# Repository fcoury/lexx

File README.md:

# KobitoKey-inspired folding keyboard

## Expanded hot-swap keyboards

Both editions have **58 south-facing switches**, a 19.05 mm finger pitch, and three folding thumb keys per hand. Choose the PCBs, plates and sockets for your switches.

| Switch edition | Complete package | Build guide |
| --- | --- | --- |
| Full-height MX · revision B | [Download MX](Expanded-MX-PCB.zip) | [MX parts and assembly](pcb/README.md) |
| Low-profile Kailh Choc V2 | [Download Choc V2](Expanded-Choc-V2-PCB.zip) | [Choc V2 parts and assembly](choc-v2/README.md) |

## Hand-wired MX case

The standard model preserves the 17 finger positions and three-key thumb fan on each hand. The expanded model adds a far row and an outer column to the main grid, bringing each hand to 29 switches. Both use the same thumb shell, hinge and thumb plate. The instructions below cover the hand-wired mechanical prototype. The [hinge sourcing notes](hinge-sourcing.md) cover two commercial torque-hinge candidates.

## Layout and source

The standard finger matrix uses 19.05 mm pitch. The three thumb switches follow the original fan in front of the inner finger columns. Their center spacing scales with the original layout, so it is wider than one finger-key pitch. The return beside the finger deck is closed for this trackball-free build. A future sensor, ball retainer and controller mount would require their own mechanical design.

The switch positions came from measurements of the maker’s v1.0.1 plate openings. Coordinates below are for the left hand, relative to the innermost front finger switch. Positive X points inward and positive Y points toward the far row. The right hand mirrors X and yaw.

| Thumb key | X at MX scale | Y at MX scale | Yaw |
|---|---:|---:|---:|
| Under finger bank | −12.70 mm | −38.83 mm | 0° |
| Middle | +10.33 mm | −41.64 mm | −14° |
| Inner tip | +32.02 mm | −49.96 mm | −28° |

The extra row sits beyond the existing back row. The new outer column follows the pinky stagger. All 20 original positions stay fixed relative to the index key. In the saved files, the added nine cap proxies per hand form a separate object named `fixed_caps_added`.

[Measured layout overlay](layout-fit.png) · [Maker’s CAD release](https://github.com/juichi50iii/KobitoKey_QWERTY/releases/tag/v1.0.1) · [Product site](https://juichi50iii.github.io/kobitokey-site/) · [Kit listing](https://iikagen-11.booth.pm/items/7511680)

## Open and pose

1. Open `models/Standard.blend` or `models/Expanded.blend`. The **Controls** object is selected.
2. In **Object Properties → Custom Properties**, drag **thumb_fold_deg** or enter a number from 0 to 60. The finger deck stays fixed in this editing scene.
3. To inspect both hands, use Blender’s scene selector to switch to **Split keyboard** and press **Home** over the viewport to frame the pair. The right half mirrors edits and fold adjustments to the left.
4. Hide the purchased-parts collection to inspect the bare case. The shaded switches and dished caps are fit and visualization proxies. Every printable part is a separate mesh. The source scripts are included alongside the models and in Blender’s Text Editor.

The angle is between decks. For use at 60°, tip the entire half onto the outer edges of both shells to form a tent. The main deck then sits roughly 12° above the desk on the standard half and 11° on the expanded half. The indexed lock holds **flat or folded**. Remove the locking screw to move between those positions.

## Print and assemble

Print one each of the four STLs in each hand folder for the chosen variant, eight parts per keyboard. The hand-specific files are already mirrored. Import in millimeters at 100%. The shells are floor-down and the removable plates are top-face-down with their posts pointing up. The nominal switch openings are 14.00 mm square through a 1.50 mm plate.

| Per half | Quantity | Fit |
|---|---:|---|
| MX-compatible 1u switches and caps | 20 standard or 29 expanded | 18.2 mm square keycap envelope used for fold testing |
| M3 × 50 socket-head screw and M3 nyloc nut | 1 each | Axle, 3.5 mm printed bores, head up to Ø5.5 × 3 mm, nut up to Ø6.4 × 4 mm; no washers |
| M3 × 10 socket-head screw | 1 | Removable angle lock, same head envelope |
| M3 brass heat-set insert | 1 | Ø4.0 × 4.0 mm body, Ø3.65 mm modeled pilot. Match the insert supplier’s pilot recommendation to your material |
| M2.5 × 8 countersunk plastic thread-forming screws | 9 | Five finger plate posts and four thumb plate posts, 2.1 mm blind pilot, 90° countersink, head diameter up to 5.1 mm |

1. Print one thumb plate to check switch retention and one shell pair to check the hinge before committing to the full keyboard. PETG with a 0.4 mm nozzle, 0.2 mm layers and four walls is a starting point for shells. Use a layer height that reproduces the 1.5 mm plate thickness, such as 0.15 mm. Support the horizontal knuckles locally and clear their bores before assembly.
2. With the thumb shell detached, press the heated insert flush into its **single offset bore**, from the rear (+Y) face of the moving ear. The main shell’s matching ear has two offset holes. The central holes take the axle.
3. Interleave the knuckles with the shells flat. Lift the case and hold the axle nut against the forward fixed ear from below. Feed the M3 × 50 axle from the rear. Leave it free enough to pivot without pulling the knuckles together.
4. Snap switches into the plates and hand-wire them. Use the paired rear ports for a flexible external service loop behind the hinge. Route the host/controller lead through the separate rear opening on the finger shell. Size and secure the loop on the actual assembly across the full fold. Electronics, strain relief and a controller-specific cradle are left to the builder.
5. Lower each plate onto its shell and fit the M2.5 screws from underneath. At 0° or 60°, pass the M3 × 10 locking screw through the aligned fixed-ear hole and into the insert. Remove it fully before changing angle.

[Exploded view](case-parts.png)

## Verification and limits

Both editable models were generated and reopened with Blender 5.2.4 LTS. The fold validator evaluates both ends and 119 intermediate poses. It checks every fixed mesh against every moving mesh, including hidden 18.2 mm full-stroke switch/keycap envelopes and the axle. The continuous lower bound subtracts the maximum possible motion between samples. The second hand is an exact reflection.

The smallest sampled gap was 0.248 mm at the axle. The conservative lower bound over the whole fold was 0.205 mm there and 0.4995 mm between printed parts.

The STL checker reads each exported file independently, tests topology and self-intersections, and probes switch apertures, mounting holes, switch-body clearance and cable passages. A separate hardware check examines screw, nut and insert fit and access. The reports record file hashes and the assumptions used.

No physical print, typing-load test, wire-flex life test or printer-tolerance study has been performed. Printer shrinkage, cap profile, switch clips and insert dimensions can change the fit.

[Standard fold report](validation/Standard.json) · [Expanded fold report](validation/Expanded.json) · [Hardware report](validation/hardware.json) · [STL report](validation/parts.json)

## Rebuild

From this folder, using fish on macOS, run the following commands. In Codex on this Mac, run all Blender commands outside the sandbox per AGENTS.md.

```fish
set blender_bin /Applications/Blender.app/Contents/MacOS/Blender
$blender_bin -b --factory-startup --python-exit-code 1 --python build.py
for variant in Standard Expanded
    $blender_bin -b models/$variant.blend --python-exit-code 1 --python validate_fold.py -- --max-step 0.5 --output validation/$variant.json
end
$blender_bin -b --factory-startup --python-exit-code 1 --python validate_hardware.py
python3 validation/check_parts.py
python3 preview.py
```

The STL checker uses NumPy. The preview script uses Pillow and invokes Blender to render the saved models.

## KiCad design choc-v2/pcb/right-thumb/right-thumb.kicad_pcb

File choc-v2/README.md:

# Expanded Choc V2 keyboard

This low-profile split uses **58 south-facing Kailh Choc V2 switches**. Each hand has 26 finger keys and a folding three-key thumb fan. It keeps the 19.05 mm finger pitch, key centers and thumb angles of the expanded MX keyboard. The Choc plate sits 2.20 mm above the top of the PCB, 2.80 mm closer than the MX plate. Both editions use the indexed M3 hinge and a separate wireless controller per hand.

## Parts for one keyboard

Use 58 **Kailh PG1353** switches, 58 **Kailh CPG135001S30** hot-swap sockets and 58 low-profile 1u keycaps specified for the Choc V2 cross stem. Red linear **CPG135301D01** is the dimensional reference for this version. The asymmetric retention slot is on the LED side. The switch windows face the typist from the keycap side and follow each thumb key’s angle. This version has no per-key LED circuit. [Switch drawings](https://www.kailh.net/pages/product-datasheet) · [Socket drawing](https://cdn-shop.adafruit.com/product-files/5118/5118-Choc-Socket.pdf) · [Purchasing BOM](BOM.csv)

| Board (one each) | Editable KiCad project | Gerbers and drills |
| --- | --- | --- |
| Left finger | [Project](pcb/left-finger/left-finger.kicad_pro) | [Fabrication ZIP](pcb/fabrication/left-finger-fabrication.zip) |
| Left thumb/controller | [Project](pcb/left-thumb/left-thumb.kicad_pro) | [Fabrication ZIP](pcb/fabrication/left-thumb-fabrication.zip) |
| Right finger | [Project](pcb/right-finger/right-finger.kicad_pro) | [Fabrication ZIP](pcb/fabrication/right-finger-fabrication.zip) |
| Right thumb/controller | [Project](pcb/right-thumb/right-thumb.kicad_pro) | [Fabrication ZIP](pcb/fabrication/right-thumb-fabrication.zip) |

[View the routed boards](pcb/preview.png) · [Switch, fabrication and firmware checks](validation/README.md)

## Build a first pair

1. **Test one switch.** Print the [one-switch fit coupon](case/choc-fit-coupon.stl) using the same filament, layer height and slicer compensation you intend to use for the plates. Check that the rim rests flat, the clips engage, and your keycap reaches full travel without rubbing. Print the [two A4 fit sheets](fit-sheets.pdf) at Actual Size and check the 50 mm bar with a ruler.
2. **Print one hand.** Select its fixed shell, fixed plate, thumb shell and thumb plate from the [case files](case/print/). Dry-fit the hardware and boards, starting with the moving thumb deck. To inspect the assembly digitally, select Controls in the [Blender model](case/Expanded-Choc-V2.blend) and adjust the thumb fold angle from 0° to 60°. Install the angle-lock screw for use at 0° or 60°.
3. **Order four different boards.** Upload each fabrication ZIP separately. Specify two-layer 1.6 mm FR-4, 1 oz copper and unplated routed slots. Check each handed outline and verify the offset retention slots in the fabricator’s drill preview. The placement CSVs and inspection reports accompany the [fabrication archives](pcb/fabrication/).
4. **Assemble the backs.** Fit a Choc socket and SOD-123 diode at each switch position. The diode band goes to pad 1. Fit the Hirose J1 flex connector on each board. Fit the XIAO nRF52840 directly to its lands (including underside battery and ground lands), S1, and the J2 battery jack on each thumb board. Assemble the matrix first on USB. The XIAO modules provide USB-C, battery charging and Bluetooth. [Controller documentation](https://wiki.seeedstudio.com/XIAO_BLE/)
5. **Connect and test.** Fit a 12-position 0.50 mm-pitch ribbon with opposite-side contacts and 0.30 mm mating tips. With power off, check J1 pin 1 to pin 1 through 12 to 12. Check for shorts between the battery supply and ground. Check J2 lead polarity before fitting an optional protected cell. Flash the [left and right firmware](firmware/README.md), test all 29 positions per hand and support each socket while inserting its switch.
6. **Exercise the fold.** Route a slack loop behind the hinge and protect it at the shell openings. With the angle-lock screw removed, move slowly through the range and check for cable tension, creasing, rubbing, desk contact and dropped keys. The rigid-part simulation leaves cable flex life, print tolerances, radio range and assembled operation for a physical prototype. [Case and fold checks](case/README.md)

## Editing

Keep each KiCad project beside the supplied symbol, footprint and model libraries. The four native boards are the manufacturing masters. The [firmware configuration](firmware/config/) contains the matrix and three keymap layers. The build uses the name **Lexx Choc V2** over Bluetooth so you can distinguish it from **Lexx MX**.

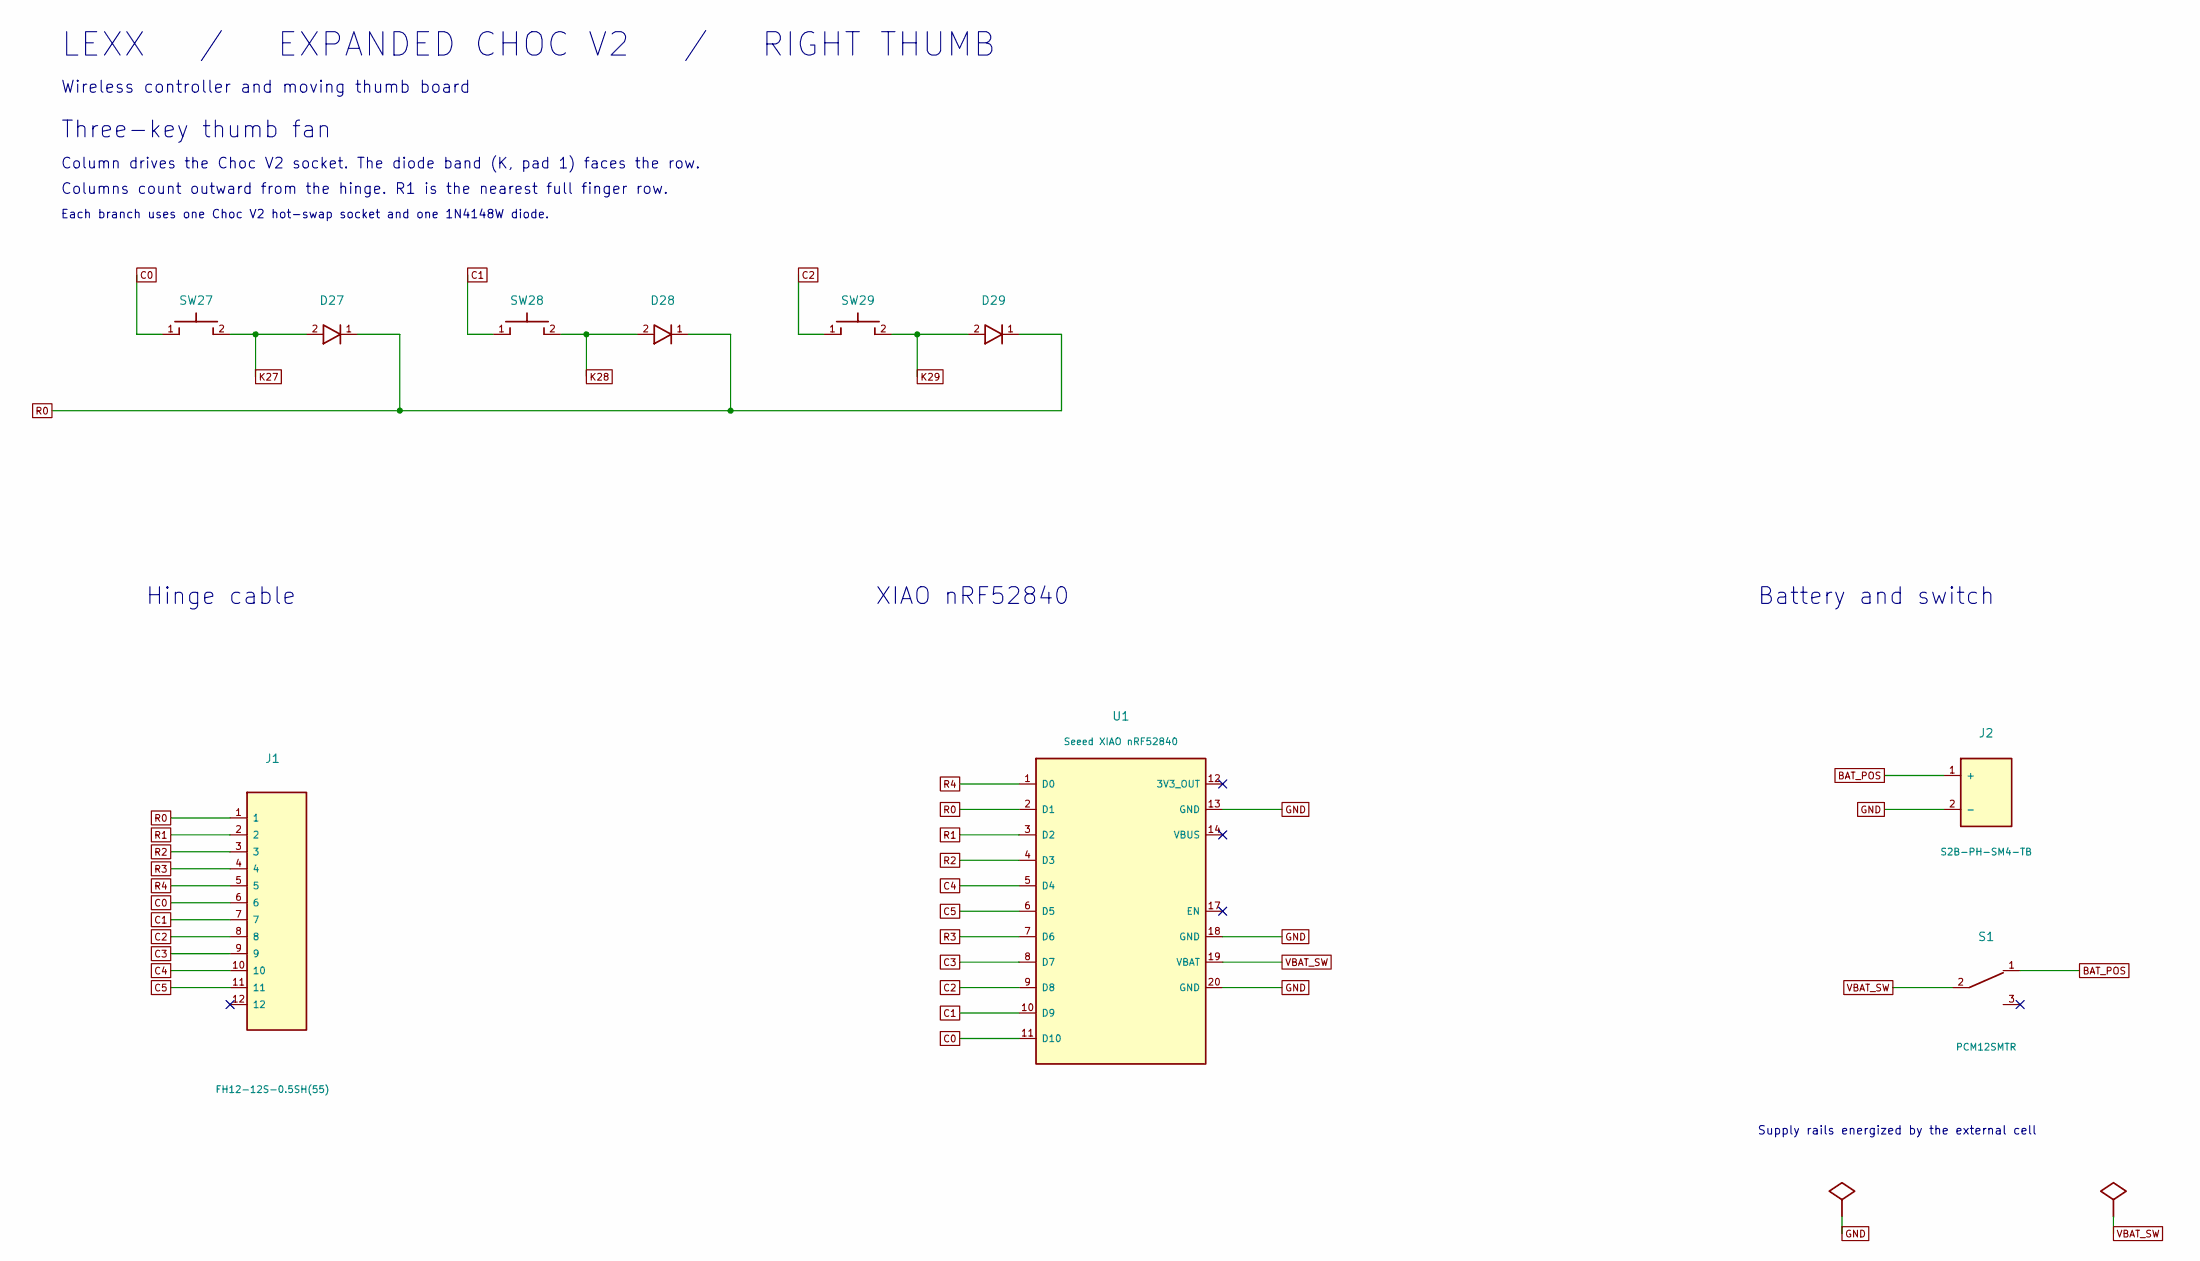
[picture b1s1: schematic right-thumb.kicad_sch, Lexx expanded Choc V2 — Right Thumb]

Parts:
D27, D28, D29: 1N4148W; SOD123
J1: FH12-12S-0.5SH(55); FFC12
J2: S2B-PH-SM4-TB; Battery
S1: PCM12SMTR; PowerSwitch
SW27, SW28, SW29: PG1353 / CPG135001S30; ChocV2
U1: Seeed XIAO nRF52840; XIAO

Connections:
BAT_POS: J2.1 (+), S1.1
C0: J1.6, SW27.1, U1.11 (D10)
C1: J1.7, SW28.1, U1.10 (D9)
C2: J1.8, SW29.1, U1.9 (D8)
C3: J1.9, U1.8 (D7)
C4: J1.10, U1.5 (D4)
C5: J1.11, U1.6 (D5)
GND: J2.2 (−), U1.13 (GND), U1.18 (GND), U1.20 (GND)
K27: D27.2 (A), SW27.2
K28: D28.2 (A), SW28.2
K29: D29.2 (A), SW29.2
R0: D27.1 (K), D28.1 (K), D29.1 (K), J1.1, U1.2 (D1)
R1: J1.2, U1.3 (D2)
R2: J1.3, U1.4 (D3)
R3: J1.4, U1.7 (D6)
R4: J1.5, U1.1 (D0)
VBAT_SW: S1.2 (COM), U1.19 (VBAT)

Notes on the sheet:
Three-key thumb fan
Column drives the Choc V2 socket. The diode band (K, pad 1) faces the row.
Columns count outward from the hinge. R1 is the nearest full finger row.
Each branch uses one Choc V2 hot-swap socket and one 1N4148W diode.
LEXX / EXPANDED CHOC V2 / RIGHT THUMB
Wireless controller and moving thumb board
Hinge cable
XIAO nRF52840
Battery and switch
Supply rails energized by the external cell

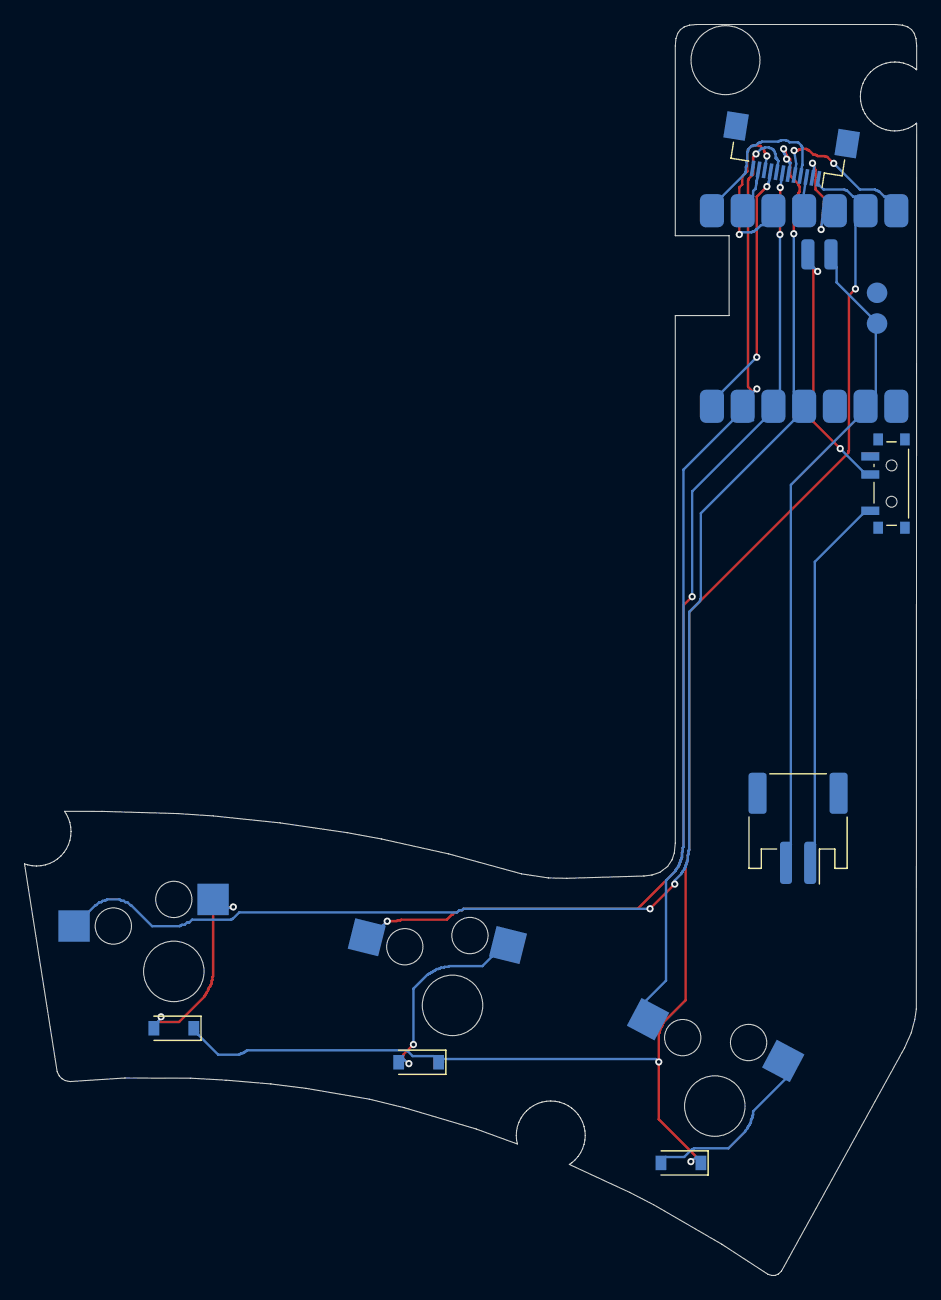
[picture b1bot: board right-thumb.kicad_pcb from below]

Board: 2 copper layers, 73.8 x 103.4 mm, 10 parts (10 on the bottom side), 17 nets.

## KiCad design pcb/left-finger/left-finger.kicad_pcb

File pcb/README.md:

# Expanded MX hot-swap PCB · Revision B

All **58 MX switches face south**. Looking down at the keys, the LED window sits on the edge nearest the typist. Each thumb switch follows its angled keycap. This revision uses Kailh hot-swap sockets and has no per-key lighting circuit.

Each hand has a passive 26-key finger PCB and a three-key moving thumb PCB. The thumb board carries a Seeed XIAO nRF52840, USB-C, the battery connector and the power switch. One 12-conductor flex cable connects the two boards within a hand. The left and right controllers communicate over Bluetooth. Revision B retains the original 19.05 mm finger pitch and three thumb centers, and uses the indexed 0–60° hinge.

[View the copper layers on all four boards](preview.png).

The [populated left-hand underside](left-assembly.png) shows the Kailh sockets and the thumb controller at their flat-case positions. The controller and battery connector use simplified package models.

## Files for one keyboard

| Board | Editable KiCad 10 project | Fabrication archive | Quantity |
| --- | --- | --- | --- |
| Left finger | [Project](left-finger/left-finger.kicad_pro) | [Gerbers and drills](fabrication/left-finger-fabrication.zip) | 1 |
| Left thumb/controller | [Project](left-thumb/left-thumb.kicad_pro) | [Gerbers and drills](fabrication/left-thumb-fabrication.zip) | 1 |
| Right finger | [Project](right-finger/right-finger.kicad_pro) | [Gerbers and drills](fabrication/right-finger-fabrication.zip) | 1 |
| Right thumb/controller | [Project](right-thumb/right-thumb.kicad_pro) | [Gerbers and drills](fabrication/right-thumb-fabrication.zip) | 1 |

Keep the project folders together with the shared symbol and footprint libraries. Each project contains its own editable schematic and routed board. Each archive describes a separate **two-layer, 1.6 mm FR-4 bare PCB**. Specify 1 oz copper. Import all layers and both drill types in millimeters and preserve handedness.

Use the [purchasing BOM](BOM.csv), [PCB case and printable shells](case/README.md), [production files and placement CSVs](fabrication/) and [firmware and flashing instructions](firmware/README.md). Use the revision B finger shells and finger plates together. The central screw moves 3.77 mm toward the rear, and the rear edge extends around the relocated flex connector. The [case print guide](case/README.md) identifies the matching parts for both hands.

## What follows the original

The original kit and build guide establish the two-board layout, flexible link, controller location and diode matrix. The published firmware gives the XIAO GPIO assignments. The maker's public release provided case models and firmware. The schematics, routing, hot-swap placements and expanded matrix here were designed for the new MX case. The nine added switches per hand need six columns and five rows. The original 10-position flex is too small for that passive matrix. All 11 header GPIOs now serve the keyboard, so a later trackball requires a new interface. [Design sources and footprint credits](ATTRIBUTION.md)

| J1 pin | 1 | 2 | 3 | 4 | 5 | 6 | 7 | 8 | 9 | 10 | 11 | 12 |
| --- | --- | --- | --- | --- | --- | --- | --- | --- | --- | --- | --- | --- |
| Signal | R0 | R1 | R2 | R3 | R4 | C0 | C1 | C2 | C3 | C4 | C5 | unused |
| XIAO pin | D1 | D2 | D3 | D6 | D0 | D10 | D9 | D8 | D7 | D4 | D5 | — |

Each switch connects a column to the anode of its diode. The cathode connects to the row. R0/C0 through R0/C2 are the original thumb fan. The two lower pinky-side finger positions occupy R0/C3 and R0/C4. R0/C5 is open. SW1–SW26 live on the finger PCB. SW27–SW29 live on the thumb PCB. Reference numbers repeat on the opposite hand.

## Assemble and bring up the first pair

1. **Check fit on paper.** Print the [two A4 fit sheets](expanded-mx-fit-sheets.pdf) at actual size. Measure the 50 mm scale bar and align the switch centers and post holes against the matching revision B plate. The marks beside the centers identify the LED-window side. Use the revised shells for access to USB, the battery switch and the flex.
2. **Populate the backs.** Fit the bottom-side Kailh sockets and SOD-123 diodes. The cathode band goes to pad 1. Both J1s use the same Hirose bottom-contact socket. The XIAO's own USB-C jack points toward the outer side of the thumb return. Fit the module directly to its lands without pin headers. Paste/reflow the required underside battery and ground lands with the castellations. The USB data lines and charge controller are on the module. [Kailh MX socket](https://www.kailhswitch.com/info/kailh-pcb-socket-for-switch-37972215.html) · [Hirose connector drawing](https://www.hirose.com/product/p/CL0586-0704-0-55) · [Seeed controller documentation](https://wiki.seeedstudio.com/XIAO_BLE/)
3. **Fit the flex.** Use 12 ways, 0.50 mm pitch, opposite-side exposed contacts and 0.30 mm mating tips. A 102 mm jumper is the starting length. Insert both ends fully and close both latches. With power disconnected, check J1 pad 1 to pad 1, then 2 to 2 through 12 to 12. Route a slack loop through the two rear openings and behind the axle. The flex should stay clear of the screws and desk throughout the fold. Check the cable supplier's dynamic bend limits. [Molex candidate](https://www.molex.com/en-us/products/part-detail/150782412)
4. **Check power without a battery.** On the unpowered board, check for shorts between BAT_POS, VBAT_SW, ground and the module's 3V3 pad. S1 should connect J2 pin 1 to U1 pad 19 in only one position. J2 pin 2 should connect to ground in either position. Power each XIAO by USB and flash the matching [left](firmware/bin/lexx_left.uf2) or [right](firmware/bin/lexx_right.uf2) image. Pair the halves. Momentarily bridge the two switch contacts at each position to test the matrix before installing the switches.
5. **Install the switches.** Looking down at a flat hand with the thumb keys nearest you, point each LED window toward you. On an angled thumb key, the LED window follows the near edge of that keycap. Align the two metal pins with the socket openings before pressing. Support the socket from behind during installation. Check the chosen keycap profile through a full stroke on the narrow pinky column and the three thumb keys.
6. **Fit the optional batteries.** Use one protected 1S LiPo per side, within the case's 18 × 24 × 4 mm body envelope, with a charge-current rating suitable for the XIAO. Verify the actual lead polarity with a meter before mating the plug. Pin 1 is positive. Pin 2 is ground. The battery charges through the XIAO when S1 connects it. S1 disconnects the battery in the other position. USB can still power the module. Secure the pack and leave the plug, flex and antenna clear.
7. **Exercise the hinge.** Test several chords across both halves at 0° and 60°. Move slowly through intermediate positions with the index screw removed. Check for key dropouts, cable tension, creasing or rubbing. Verify wireless range and check USB plug access with the cable and shell you plan to use.

## Verification and scope

KiCad's ERC checks the schematic. DRC checks the board geometry and copper connections, including schematic parity. All four boards passed ERC and DRC with zero warnings, errors, open connections or schematic mismatches. The per-board reports live beside the Gerbers. The case checks compare the actual board outlines with the printed shells and plate posts. Each board sits with its top 5 mm beneath the plate top. The smallest PCB-to-shell gap is 0.38 mm. The socket bodies clear the shell by at least 0.99 mm. Both hands retain at least 1.0 mm of clearance between the rigid electronics and the opposing deck or hinge hardware through 0–60°. [Measured case fit](case/board-fit.json) · [Rigid fold sweep](case/fold.json) · [Electronics fold sweep](case/electronics-fold.json)

The fold sweep covers the rigid parts and switch/keycap envelopes. Cable fatigue, battery-lead routing, RF range, USB plug overmold clearance, typing load, solder assembly and printer tolerance need physical testing. The printable shells use the indexed M3 hinge. The optional Ø4 × 11 mm commercial hinge takes a separate keyed mount.

## Recheck a design

Open a project in KiCad to edit the schematic or copper. To check all four projects from a terminal, put KiCad 10's CLI on PATH and run these commands from this directory.

```fish
python3 tools/verify_matrix.py
for board in left-finger left-thumb right-finger right-thumb
    kicad-cli sch erc --exit-code-violations -o /tmp/$board-erc.rpt $board/$board.kicad_sch
    kicad-cli pcb drc --schematic-parity --exit-code-violations -o /tmp/$board-drc.rpt $board/$board.kicad_pcb
end
```

Run `tools/verify_switches.py` with KiCad’s Python interpreter (`pcbnew`) to check the physical contact and locating holes against the intended LED-window direction, key centers, and matrix. To regenerate the A4 fit sheets, run `python3 tools/fit_sheet.py --kicad-python /path/to/kicad/python3` with ReportLab available to the outer interpreter.

The routed KiCad boards are the manufacturing masters. To replot one, use KiCad's Python interpreter with the `pcbnew` module and run `tools/route_and_plot.py left-finger/left-finger.kicad_pcb --output fabrication`. For a new layout, use a separate checkout. `tools/plan.py` (Python with Shapely) derives the outlines from the case. `tools/schematics.py` builds the diagrams from the pin manifests and `tools/place.py` builds fresh, unrouted boards with KiCad's Python. Routing includes hand finishing. Recheck schematic parity, copper, physical fit and the firmware matrix after changing geometry.

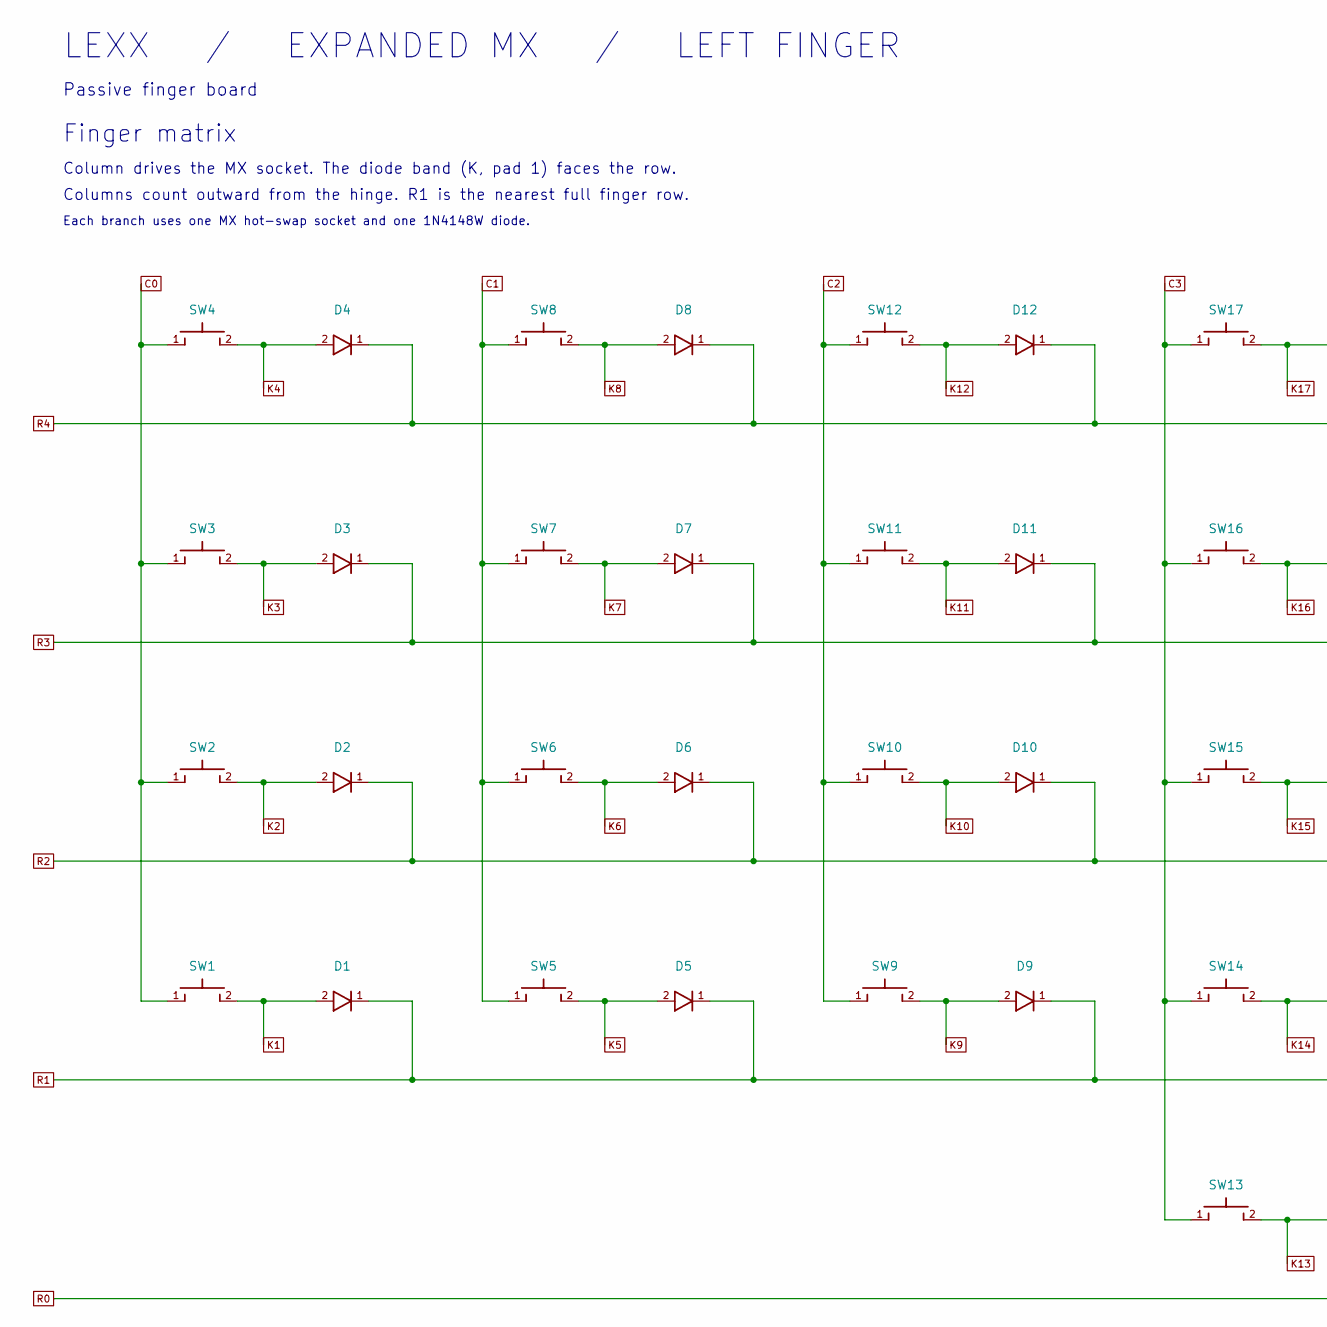
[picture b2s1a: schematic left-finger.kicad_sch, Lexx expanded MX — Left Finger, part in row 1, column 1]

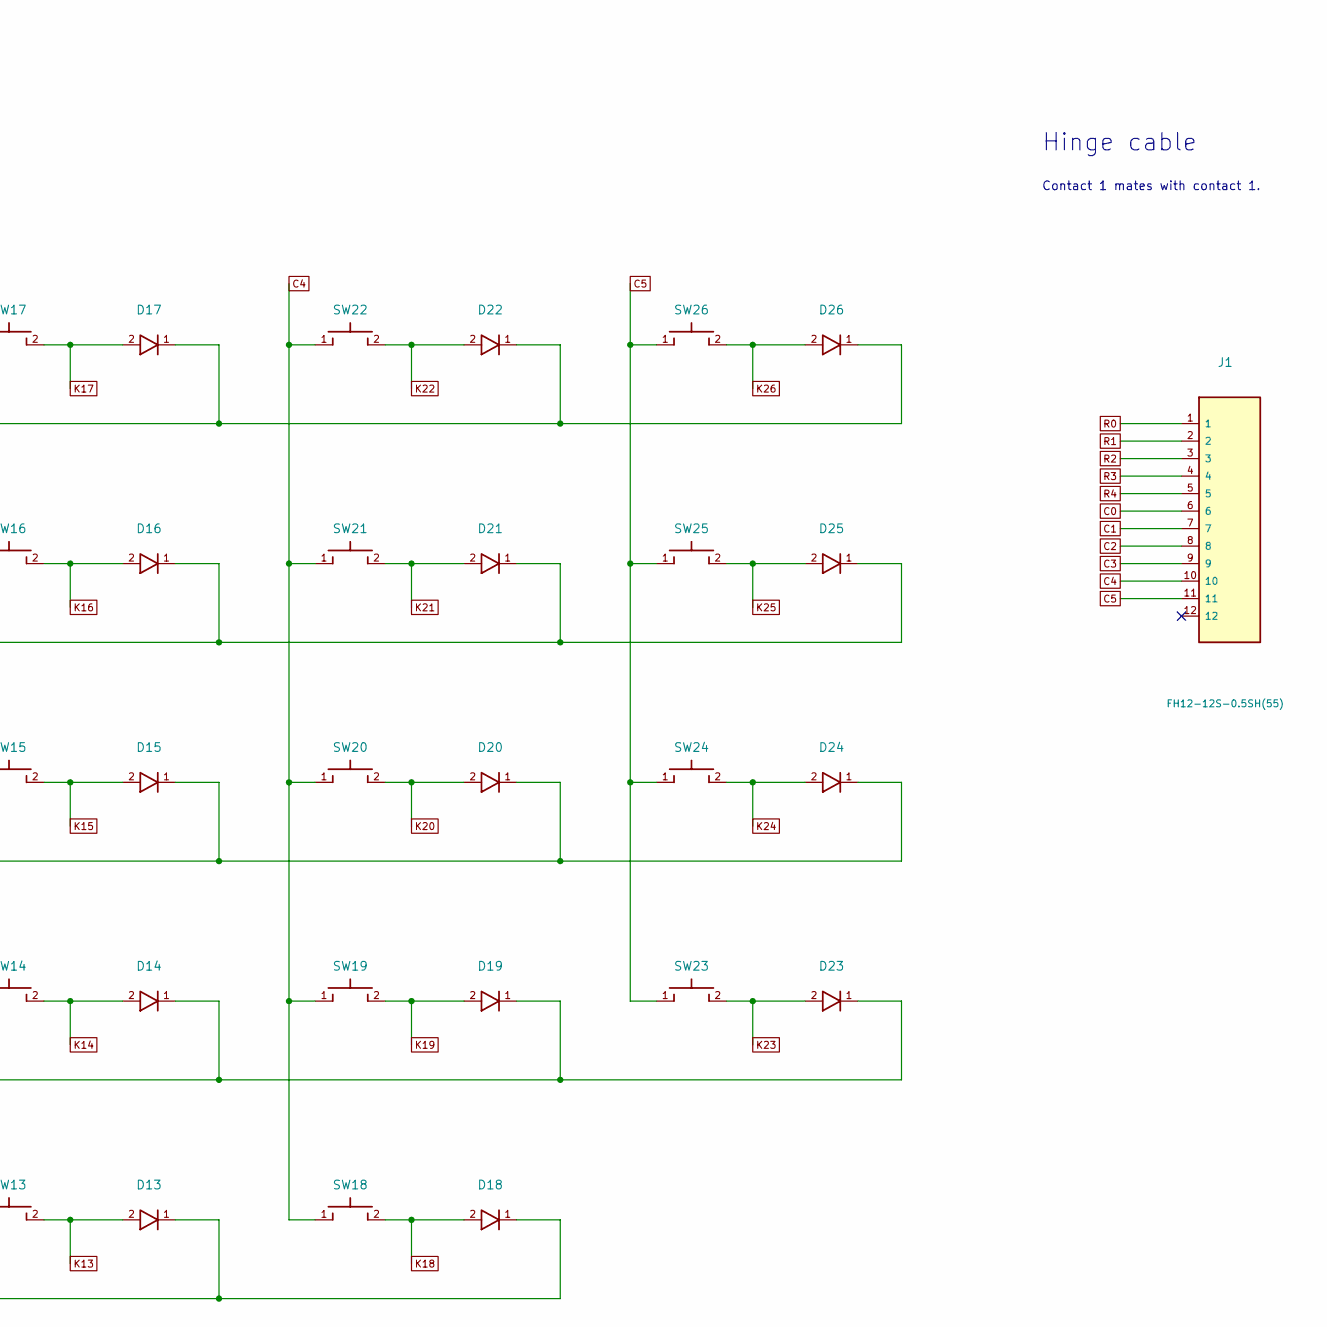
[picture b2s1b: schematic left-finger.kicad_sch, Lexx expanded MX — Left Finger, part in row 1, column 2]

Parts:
D1, D2, D3, D4, D5, D6, D7, D8, D9, D10, D11, D12, D13, D14, D15, D16, D17, D18, D19, D20, D21, D22, D23, D24, D25, D26: 1N4148W; SOD123
J1: FH12-12S-0.5SH(55); FFC12
SW1, SW2, SW3, SW4, SW5, SW6, SW7, SW8, SW9, SW10, SW11, SW12, SW13, SW14, SW15, SW16, SW17, SW18, SW19, SW20, SW21, SW22, SW23, SW24, SW25, SW26: MX hot-swap; MX

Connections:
C0: J1.6, SW1.1, SW2.1, SW3.1, SW4.1
C1: J1.7, SW5.1, SW6.1, SW7.1, SW8.1
C2: J1.8, SW9.1, SW10.1, SW11.1, SW12.1
C3: J1.9, SW13.1, SW14.1, SW15.1, SW16.1, SW17.1
C4: J1.10, SW18.1, SW19.1, SW20.1, SW21.1, SW22.1
C5: J1.11, SW23.1, SW24.1, SW25.1, SW26.1
K1: D1.2 (A), SW1.2
K2: D2.2 (A), SW2.2
K3: D3.2 (A), SW3.2
K4: D4.2 (A), SW4.2
K5: D5.2 (A), SW5.2
K6: D6.2 (A), SW6.2
K7: D7.2 (A), SW7.2
K8: D8.2 (A), SW8.2
K9: D9.2 (A), SW9.2
K10: D10.2 (A), SW10.2
K11: D11.2 (A), SW11.2
K12: D12.2 (A), SW12.2
K13: D13.2 (A), SW13.2
K14: D14.2 (A), SW14.2
K15: D15.2 (A), SW15.2
K16: D16.2 (A), SW16.2
K17: D17.2 (A), SW17.2
K18: D18.2 (A), SW18.2
K19: D19.2 (A), SW19.2
K20: D20.2 (A), SW20.2
K21: D21.2 (A), SW21.2
K22: D22.2 (A), SW22.2
K23: D23.2 (A), SW23.2
K24: D24.2 (A), SW24.2
K25: D25.2 (A), SW25.2
K26: D26.2 (A), SW26.2
R0: D13.1 (K), D18.1 (K), J1.1
R1: D1.1 (K), D5.1 (K), D9.1 (K), D14.1 (K), D19.1 (K), D23.1 (K), J1.2
R2: D2.1 (K), D6.1 (K), D10.1 (K), D15.1 (K), D20.1 (K), D24.1 (K), J1.3
R3: D3.1 (K), D7.1 (K), D11.1 (K), D16.1 (K), D21.1 (K), D25.1 (K), J1.4
R4: D4.1 (K), D8.1 (K), D12.1 (K), D17.1 (K), D22.1 (K), D26.1 (K), J1.5

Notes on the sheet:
Finger matrix
Column drives the MX socket. The diode band (K, pad 1) faces the row.
Columns count outward from the hinge. R1 is the nearest full finger row.
Each branch uses one MX hot-swap socket and one 1N4148W diode.
LEXX / EXPANDED MX / LEFT FINGER
Passive finger board
Hinge cable
Contact 1 mates with contact 1.

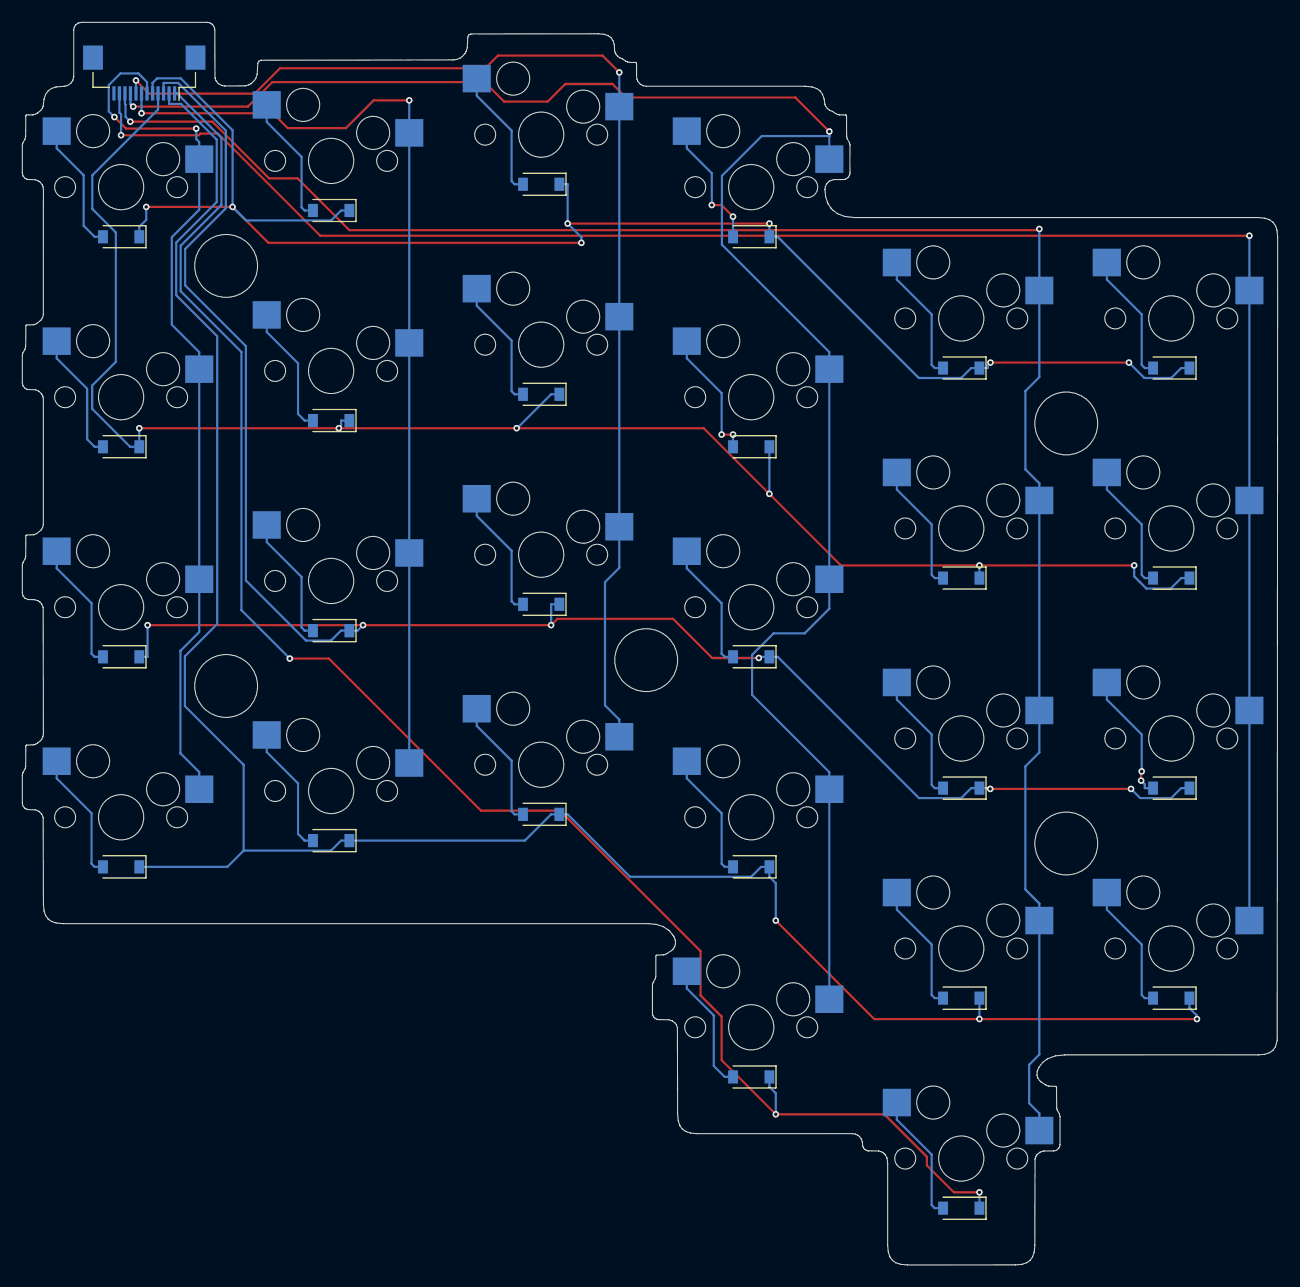
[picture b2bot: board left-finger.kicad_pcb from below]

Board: 2 copper layers, 113.9 x 112.7 mm, 53 parts (53 on the bottom side), 37 nets.
